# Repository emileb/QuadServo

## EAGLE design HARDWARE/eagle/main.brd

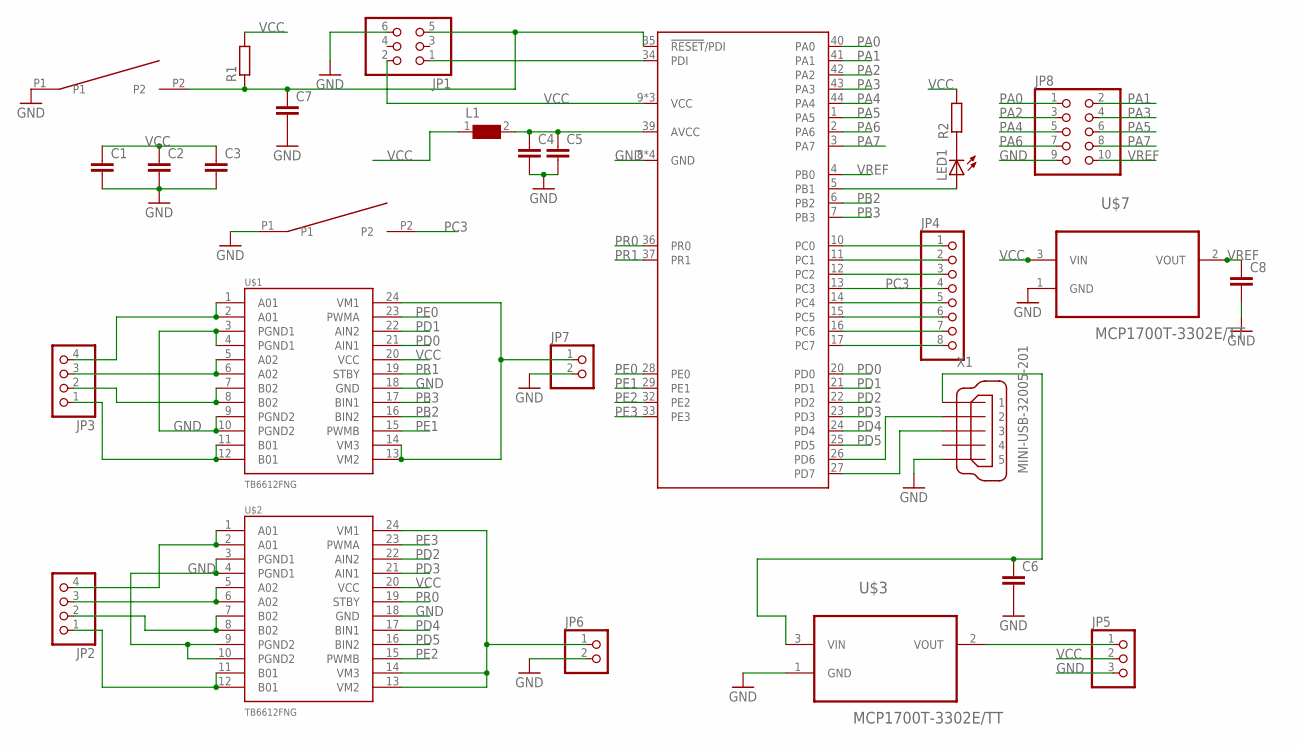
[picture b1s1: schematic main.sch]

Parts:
C1, C2, C3, C4, C5, C6, C7, C8: C-EUC0805; C0805
JP1: PINHD-2X3; 2X03
JP2, JP3: PINHD-1X4; 1X04
JP4: PINHD-1X8; 1X08
JP5: PINHD-1X3; 1X03
JP6, JP7: PINHD-1X2; 1X02
JP8: PINHD-2X5; 2X05
L1: WE-CBF-74279202_0805; 0805
LED1: LEDCHIP-LED0805; CHIP-LED0805
R1, R2: R-EU_R0805; R0805
U1: ATXMEGA32C4-AU; TQFP-44A-44
U$1, U$2: TB6612FNG; SSOP24
U$3, U$7: MCP1700T-3302E/TT; SOT95P237X112-3N
U$4, U$6: SWITCH_2PIN_SMD
X1: MINI-USB-32005-201; 32005-201

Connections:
AO1_1: JP3.4, U$1.1 (A01), U$1.2 (A01)
AO1_2: JP2.4, U$2.1 (A01), U$2.2 (A01)
AO2_1: JP3.3, U$1.5 (A02), U$1.6 (A02)
AO2_2: JP2.3, U$2.5 (A02), U$2.6 (A02)
AVCC: C4.1, C5.1, L1.2, U1.39 (AVCC)
BO1_1: JP3.1, U$1.11 (B01), U$1.12 (B01)
BO1_2: JP2.1, U$2.11 (B01), U$2.12 (B01)
BO2_1: JP3.2, U$1.7 (B02), U$1.8 (B02)
BO2_2: JP2.2, U$2.7 (B02), U$2.8 (B02)
GND: C1.2, C2.2, C3.2, C4.2, C5.2, C6.2, C7.2, C8.2, JP1.6, JP5.3, JP6.2, JP7.2, JP8.9, U1.8 (GND), U1.18 (GND), U1.30 (GND), U1.38 (GND), U$1.3 (PGND1), U$1.4 (PGND1), U$1.9 (PGND2), U$1.10 (PGND2), U$1.18 (GND), U$2.3 (PGND1), U$2.4 (PGND1), U$2.9 (PGND2), U$2.10 (PGND2), U$2.18 (GND), U$3.1 (GND), U$4.P1, U$6.P1, U$7.1 (GND), X1.5
unnamed: JP1.1, U1.34 (PDI)
unnamed: LED1.C, R2.1
unnamed: C7.1, JP1.5, R1.1, U1.35 (!RESET!/PDI), U$4.P2
unnamed: JP4.6, U1.15 (PC5)
unnamed: JP4.5, U1.14 (PC4)
unnamed: U1.26 (PD6), X1.2
unnamed: U1.27 (PD7), X1.3
unnamed: C6.1, U$3.3 (VIN), X1.1
unnamed: JP5.1, U$3.2 (VOUT)
unnamed: LED1.A, U1.5 (PB1)
unnamed: JP4.8, U1.17 (PC7)
unnamed: JP4.7, U1.16 (PC6)
unnamed: JP4.3, U1.12 (PC2)
unnamed: JP4.2, U1.11 (PC1)
unnamed: JP4.1, U1.10 (PC0)
PA0: JP8.1, U1.40 (PA0)
PA1: JP8.2, U1.41 (PA1)
PA2: JP8.3, U1.42 (PA2)
PA3: JP8.4, U1.43 (PA3)
PA4: JP8.5, U1.44 (PA4)
PA5: JP8.6, U1.1 (PA5)
PA6: JP8.7, U1.2 (PA6)
PA7: JP8.8, U1.3 (PA7)
PB2: U1.6 (PB2), U$1.16 (BIN2)
PB3: U1.7 (PB3), U$1.17 (BIN1)
PC3: JP4.4, U1.13 (PC3), U$6.P2
PD0: U1.20 (PD0), U$1.21 (AIN1)
PD1: U1.21 (PD1), U$1.22 (AIN2)
PD2: U1.22 (PD2), U$2.22 (AIN2)
PD3: U1.23 (PD3), U$2.21 (AIN1)
PD4: U1.24 (PD4), U$2.17 (BIN1)
PD5: U1.25 (PD5), U$2.16 (BIN2)
PE0: U1.28 (PE0), U$1.23 (PWMA)
PE1: U1.29 (PE1), U$1.15 (PWMB)
PE2: U1.32 (PE2), U$2.15 (PWMB)
PE3: U1.33 (PE3), U$2.23 (PWMA)
PR0: U1.36 (PR0), U$2.19 (STBY)
PR1: U1.37 (PR1), U$1.19 (STBY)
VCC: C1.1, C2.1, C3.1, JP1.2, JP5.2, L1.1, R1.2, R2.2, U1.9 (VCC), U1.19 (VCC), U1.31 (VCC), U$1.20 (VCC), U$2.20 (VCC), U$7.3 (VIN)
VCC_MOTOR2: JP6.1, U$2.13 (VM2), U$2.14 (VM3), U$2.24 (VM1)
VCC_MOTOR_1: JP7.1, U$1.13 (VM2), U$1.14 (VM3), U$1.24 (VM1)
VREF: C8.1, JP8.10, U1.4 (PB0), U$7.2 (VOUT)

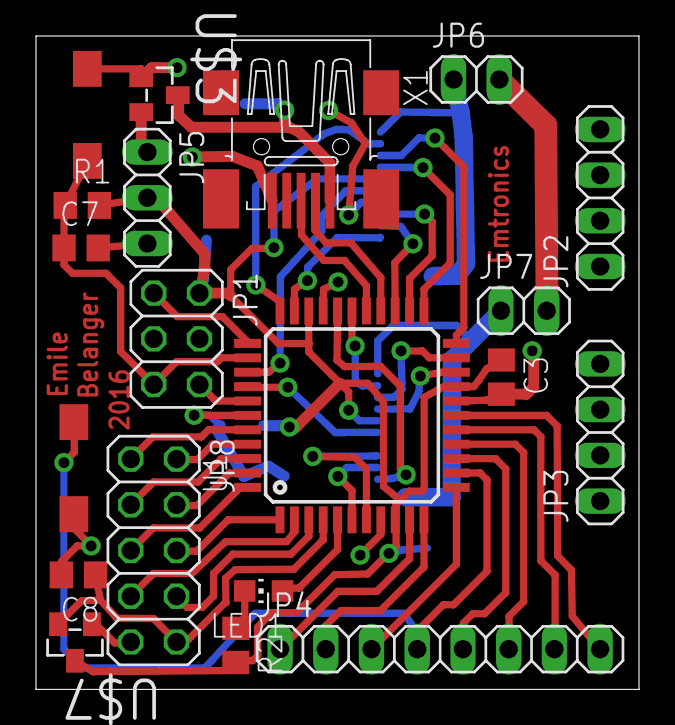
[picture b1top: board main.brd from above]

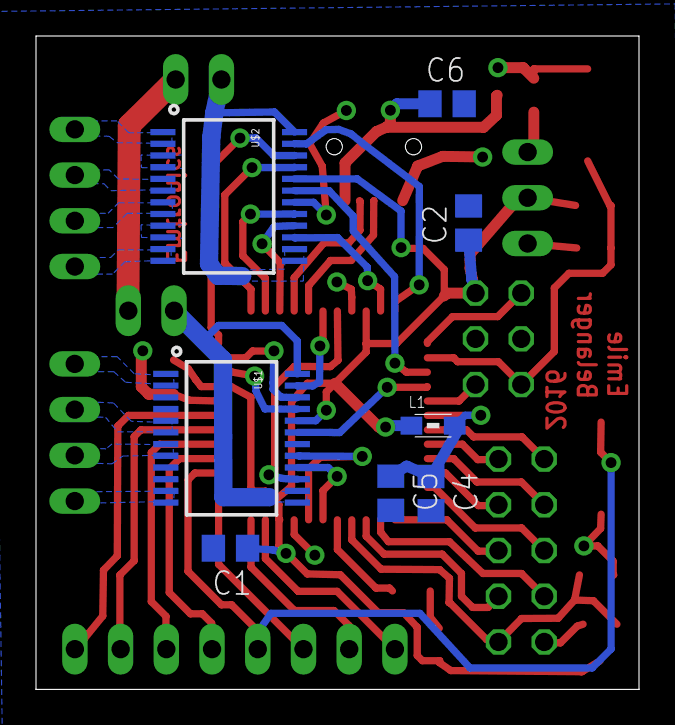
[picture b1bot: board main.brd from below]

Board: 2 copper layers, 33.5 x 36.3 mm, 28 parts (8 on the bottom side), 52 nets.

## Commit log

2017-10-15 Added project files

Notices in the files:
parts and their libraries:
SparkFun-PowerIC: Licensing: Creative Commons ShareAlike 4.0 International - https://creativecommons.org/licenses/by-sa/4.0
